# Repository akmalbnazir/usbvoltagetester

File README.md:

# 🔌 USB-C Voltage & Current Tester (RP2040 + OLED)

A USB-powered diagnostic tool that measures real-time voltage and current draw of any connected device. Designed in **KiCad**, driven by an **RP2040 microcontroller**, and visualized on a 0.96" OLED display.

## 🚀 Features
- USB-C power input
- Measures voltage via divider
- Measures current via shunt + op-amp (LM358)
- RP2040 MCU reads and displays values
- Compact 2-layer PCB, beginner-solderable

## 📦 Project Files
- `project.kicad_sch` — schematic
- `project.kicad_pcb` — board layout
- `gerbers/` — ready-to-fabricate output
- `README.md` — this doc

## 🖥️ Display
- 128x64 OLED using SSD1306 (I2C)
- SDA: GPIO0, SCL: GPIO1

## ⚙️ Future Enhancements
- USB-C PD measurement
- Onboard logging
- 3D-printed case

## 📸 Preview

## 🧑‍💻 Author
Designed by Akmal Nazir – May 2025  
MIT License

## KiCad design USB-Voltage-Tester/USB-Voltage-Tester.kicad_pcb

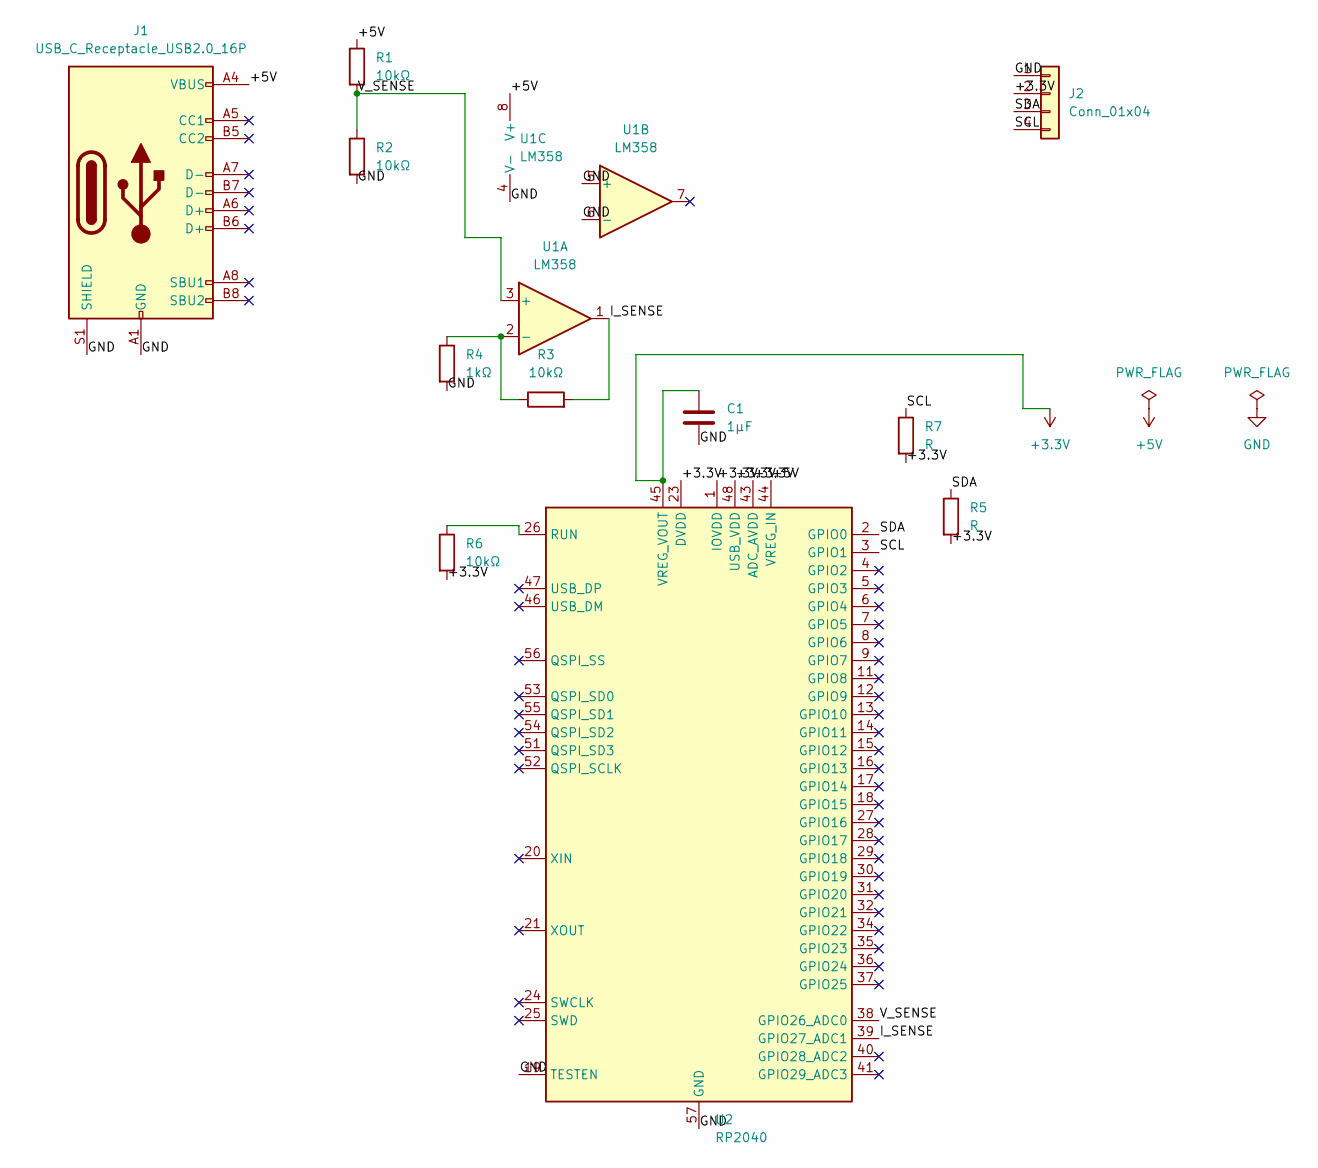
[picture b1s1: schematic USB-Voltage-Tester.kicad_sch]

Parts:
C1: 1µF; C_0805_2012Metric
J1: USB_C_Receptacle_USB2.0_16P; USB_C_Receptacle_HRO_TYPE-C-31-M-12
J2: Conn_01x04; PinHeader_1x04_P2.54mm_Vertical
R1, R2, R3, R6: 10kΩ; R_0805_2012Metric
R4: 1kΩ; R_0805_2012Metric
R5, R7: R; R_0805_2012Metric
U1: LM358; SOIC-8_3.9x4.9mm_P1.27mm
U2: RP2040; QFN-56-1EP_7x7mm_P0.4mm_EP3.2x3.2mm

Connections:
+3.3V: C1.1, J2.2, R5.2, R6.2, R7.2, U2.1 (IOVDD), U2.10 (IOVDD), U2.22 (IOVDD), U2.23 (DVDD), U2.33 (IOVDD), U2.42 (IOVDD), U2.43 (ADC_AVDD), U2.45 (VREG_VOUT), U2.48 (USB_VDD), U2.49 (IOVDD), U2.50 (DVDD)
+5V: J1.A4 (VBUS), J1.A9 (VBUS), J1.B4 (VBUS), J1.B9 (VBUS), R1.1, U1.8 (V+), U2.44 (VREG_IN)
/I_SENSE: R3.2, U1.1, U2.39 (GPIO27_ADC1)
/SCL: J2.4, R7.1, U2.3 (GPIO1)
/SDA: J2.3, R5.1, U2.2 (GPIO0)
/V_SENSE: R1.2, R2.1, U1.3 (+), U2.38 (GPIO26_ADC0)
GND: C1.2, J1.A1 (GND), J1.A12 (GND), J1.B1 (GND), J1.B12 (GND), J1.S1 (SHIELD), J2.1, R2.2, R4.2, U1.4 (V-), U1.5 (+), U1.6 (-), U2.19 (TESTEN), U2.57 (GND)
unnamed: R3.1, R4.1, U1.2 (-)
unnamed: R6.1, U2.26 (RUN)

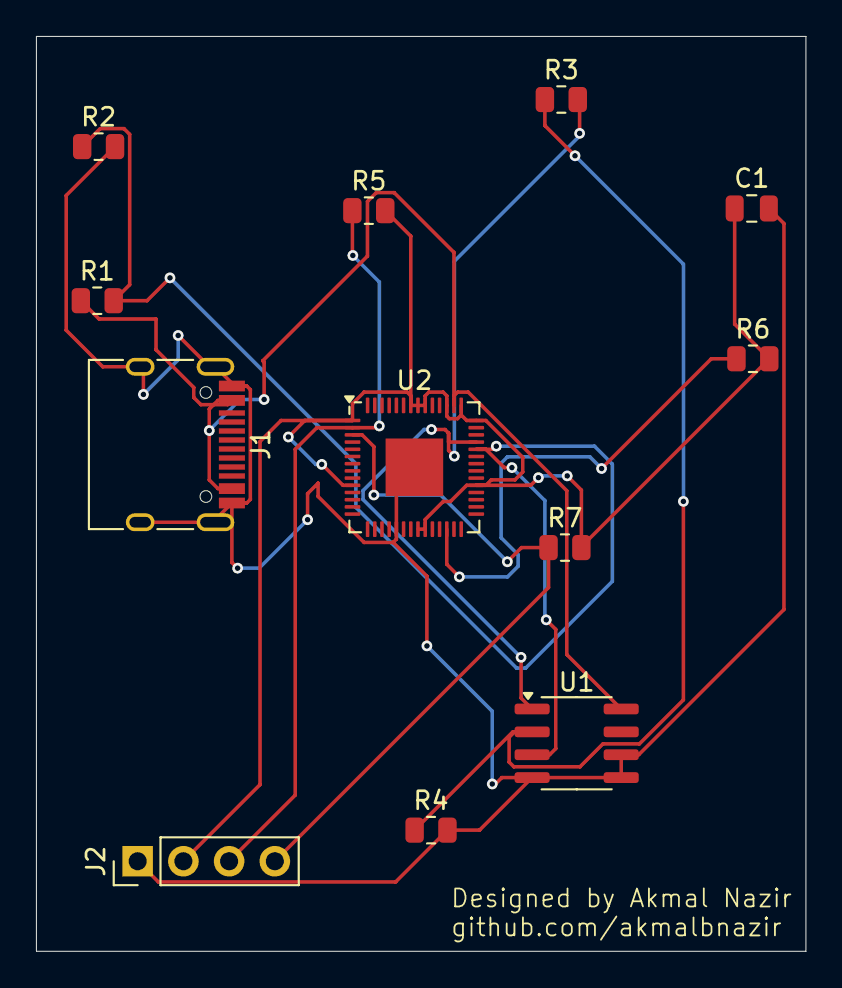
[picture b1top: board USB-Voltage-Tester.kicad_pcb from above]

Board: 2 copper layers, 42.7 x 50.8 mm, 12 parts (0 on the bottom side), 9 nets.

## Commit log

2025-05-13 Initial commit - USB Voltage & Current Tester v1
